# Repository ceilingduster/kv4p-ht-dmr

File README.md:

# VA3IAN-DMR
This modification of the KV4P-HT project is an example of swapping the SA8X8 hardware module with NiceRF's DMR818S-5W module.  This keeps the support for Analog RF on UHF or VHF (350Mhz as well in countries that support it), but adds the capability of DMR.

# Credit
Open source handheld ham radio project based on KV4p-HT by Vance Vagell (KV4P) — licensed under the GNU General Public License v3.
This product includes modifications. The full source code (including the modifications) is available at: 
https://github.com/VanceVagell/kv4p-ht

Please see the main project site: https://kv4p.com.  Thank you Vance for an incredible project!  This MOD is only meant to serve to innovate and support the greater project.

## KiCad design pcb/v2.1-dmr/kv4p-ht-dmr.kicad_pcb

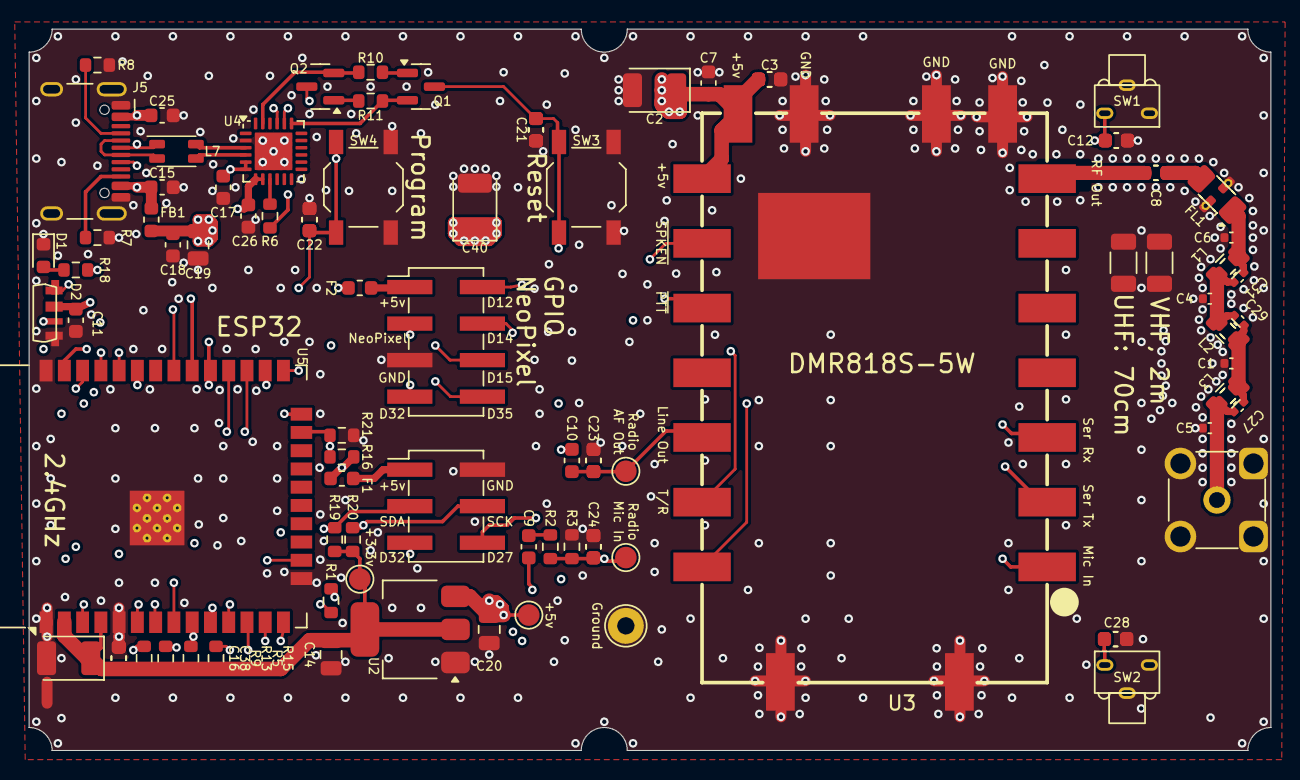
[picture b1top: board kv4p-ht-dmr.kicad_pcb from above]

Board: 4 copper layers, 86.4 x 50.2 mm, 95 parts (0 on the bottom side), 54 nets.

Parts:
C1: 18pF; C_0402_1005Metric
C2, C16, C40: 100uF 6.3v; CP_EIA-3528-21_Kemet-B
C3, C8, C12, C21, C22, C23, C24, C28, C38: 2.2nF Tuned VHF; C_0603_1608Metric
C4: 16pF; C_0402_1005Metric
C5: 10pF; C_0402_1005Metric
C6: 5.1pF; C_0402_1005Metric
C7, C11, C18, C26: 100nF; C_0603_1608Metric
C9, C10, C17: 1uF; C_0603_1608Metric
C13, C30, C32, C33, C34, C35, C36, C37, C39: 220pF Tune UHF; C_0603_1608Metric
C14, C19, C20: 10uF; C_0805_2012Metric
C15, C25: 100pF; C_0603_1608Metric
C27: 2.7pF; C_0402_1005Metric
C29: 13pF; C_0402_1005Metric
C31: 11pF; C_0402_1005Metric
D1: Red; LED_0603_1608Metric
D2: SK6812SIDE-4020; LED_SK6805_SIDE
F1, F2: 100mA; Fuse_0603_1608Metric
FB1: Ferrite Bead, 1A; L_0603_1608Metric
FL1: LFCN-490+; Filter_Mini-Circuits_FV1206
J1: Antenna; Conn_SMA_Close-to-board-edge
J2: SAO v.69bis; PinHeader_2x03_P2.54mm_Vertical_SMD
J3: GPIO Header; PinHeader_2x04_P2.54mm_Vertical_SMD
J5: USB-C Socket; USB_C_Receptacle_HCTL_HC-TYPE-C-16P-01A
L1: 27nH; L_0805_2115Metric (Murata Inductors)
L2: 30nH; L_0805_2115Metric (Murata Inductors)
L3: 43nH; L_0805_2115Metric (Murata Inductors)
L4, L5, L6: L_0603_1608Metric
L7: CMCC; L_CommonMode_Wurth_WE-CNSW-1206
Q1, Q2: SS8050; SOT-23
R1, R16, R21: 100k; R_0603_1608Metric
R2, R5, R9, R10, R11, R13, R15: 10k; R_0603_1608Metric
R3, R6, R18, R19, R20: 1.2k; R_0603_1608Metric
R4: 0R; R_1206_3216Metric
R7, R8: 5.1k; R_0603_1608Metric
R12, R14, R17: 0R; R_0603_1608Metric
R22: VHF; R_1206_3216Metric
R23: UHF; R_1206_3216Metric
SW1, SW2: PTT; SW-Push-SPST-Horizontal-C455252
SW3: Reset; SW_SPST_TL3342
SW4: Program; SW_SPST_TL3342
TP1: +5v; TestPoint_Pad_D1.5mm
TP2: +3.3v; TestPoint_Pad_D1.5mm
TP3: Gnd; TestPoint_THTPad_D2.5mm_Drill1.2mm
TP4: Radio Mic; TestPoint_Pad_D1.5mm
TP5: Radio Line Out; TestPoint_Pad_D1.5mm
U2: AZ1117H-3.3TRG1; SOT-223-3_TabPin2
U3: WIRELM-SMD_G-NICERF_DMR818-AMBE-X
U4: CP2102N-A02-GQFN24; QFN-24-1EP_4x4mm_P0.5mm_EP2.6x2.6mm
U5: ESP32-WROOM-32E-N4; ESP32-WROOM-32D

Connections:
+3.3V: C14.2, C16.1, C38.1, C39.2, R5.1, R9.2, R13.2, R15.1, R19.2, R20.2, TP2.1, U2.2 (VO), U5.2 (VDD), U5.4 (SENSOR_VP)
+5V: C2.1, C3.1, C7.1, C11.1, C18.1, C19.2, C20.2, C26.1, C30.2, C40.1, D2.2 (VDD), F1.1, F2.1, FB1.2, R16.1, TP1.1, U2.3 (VI), U3.11 (VCC), U3.12 (VCC), U4.7 (VREGIN), U4.8 (VBUS)
/ADC Bias: R1.1, U5.11 (IO26)
/Enable/~Reset: C21.1, C37.2, Q1.3 (C), R9.1, SW3.1 (A), U5.3 (EN)
/GPIO0/~Program: C22.1, C34.2, Q2.3 (C), R13.1, SW4.1 (A), U5.25 (IO0)
/GPIO12: J3.2, U5.14 (IO12)
/GPIO14: J3.4, U5.13 (IO14)
/GPIO15: J3.6, R16.2, R21.1, U5.23 (IO15)
/GPIO27: J2.6, U5.12 (IO27)
/GPIO32: J2.5, J3.7, U5.8 (IO32)
/GPIO35: J3.8, U5.7 (IO35)
/NeoPixel DI: D2.1 (DIN), U5.16 (IO13)
/NeoPixel DO: D2.3 (DOUT), J3.3
/PTT Button Left: C28.1, C36.2, R5.2, SW2.1, U5.9 (IO33)
/PTT Button Right: C12.1, C35.2, R15.2, SW1.2, U5.29 (IO5)
/Radio ANT: C8.2, C13.2, U3.7 (ANT)
/Radio CS: U3.13 (CS), U5.37 (IO23)
/Radio Line Out: C10.2, C23.1, C33.2, TP5.1, U3.16 (LINE_OUT)
/Radio Mic In: C24.1, C32.2, R2.1, R3.2, TP4.1, U3.1 (MIC_IN)
/Radio Rx: U3.3 (UART-RX), U5.28 (IO17)
/Radio SPKEN: U3.18 (SPKEN), U5.26 (IO4)
/Radio Tx: U3.2 (UART-TX), U5.27 (IO16)
/Radio T/R: U3.17 (T/R), U5.31 (IO19)
/Radio ~PTT: U3.14 (PTT), U5.30 (IO18)
/SAO SCK: J2.4, R20.1, U5.36 (IO22)
/SAO SDA: J2.3, R19.1, U5.33 (IO21)
/Stock LED: R18.1, U5.24 (IO2)
/USB Rx: U4.20 (RXD), U5.35 (TXD0/IO1)
/USB Tx: U4.21 (TXD), U5.34 (RXD0/IO3)
/~DTR: Q2.2 (E), R10.2, U4.23 (~DTR)
/~RTS: Q1.2 (E), R11.2, U4.19 (~RTS)
GND: C1.1, C2.2, C3.2, C4.1, C5.1, C6.1, C7.2, C11.2, C12.2, C14.1, C15.1, C16.2, C17.2, C18.2, C19.1, C20.1, C21.2, C22.2, C23.2, C24.2, C25.1, C26.2, C28.2, C30.1, C32.1, C33.1, C34.1, C35.1, C36.1, C37.1, C38.2, C39.1, C40.2, D1.1 (K), D2.4 (VSS), FL1.2 (GND), FL1.4 (GND), J1.2 (Ext), J2.2, J3.5, J5.A1 (GND), J5.A12 (GND), J5.B1 (GND), J5.B12 (GND), J5.S1 (SHIELD), R3.1, R7.2, R8.2, R21.2, R22.1, R22.2, R23.1, R23.2, SW1.1, SW1.SH (B), SW2.2, SW2.SH (B), SW3.2 (B), SW4.2 (B), TP3.1, U2.1 (GND), U3.8 (GND), U3.9 (GND), U3.10 (GND), U3.19 (GND), U3.20 (GND), U3.21 (EP), U4.2 (GND), U4.25 (GND), U5.1 (GND), U5.5 (SENSOR_VN), U5.15 (GND), U5.38 (GND), U5.39 (GND)
unnamed: C1.2, C27.2, C29.1, L2.1, L3.2, L4.2, L5.1, R12.1, R14.2
unnamed: C9.1, R2.2
unnamed: C4.2, C29.2, C31.1, L1.1, L2.2, L5.2, L6.1, R14.1, R17.2
unnamed: D1.2 (A), R18.2
unnamed: C6.2, C31.2, FL1.1 (IN), L1.2, L6.2, R4.2, R17.1
unnamed: C8.1, C13.1, FL1.3 (OUT), R4.1
unnamed: C5.2, C27.1, J1.1 (In), L3.1, L4.1, R12.2
unnamed: F1.2, J2.1
unnamed: F2.2, J3.1
unnamed: J5.A5 (CC1), R8.1
unnamed: J5.B5 (CC2), R7.1
unnamed: J5.A6 (D+), J5.B6 (D+), L7.1
unnamed: J5.A7 (D-), J5.B7 (D-), L7.4
unnamed: Q1.1 (B), R10.1
unnamed: Q2.1 (B), R11.1
unnamed: L7.2, U4.3 (D+)
unnamed: L7.3, U4.4 (D-)
unnamed: C17.1, R6.2, U4.5 (VIO), U4.6 (VDD)
unnamed: R6.1, U4.9 (~RST)
unnamed: C9.2, U5.10 (IO25)
unnamed: C10.1, R1.2, U5.6 (IO34)
VBUS: C15.2, C25.2, FB1.1, J5.A4 (VBUS), J5.A9 (VBUS), J5.B4 (VBUS), J5.B9 (VBUS)

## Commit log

2025-08-08 Swapped SA8X8 for DMR818S-5W
2025-08-16 Initial commit of python code example for DMR858S module
2025-08-16 Update README.md and added PCB Board
